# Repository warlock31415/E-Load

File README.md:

# E-Load
An electronic load based on the STM32F103C8T6 chip

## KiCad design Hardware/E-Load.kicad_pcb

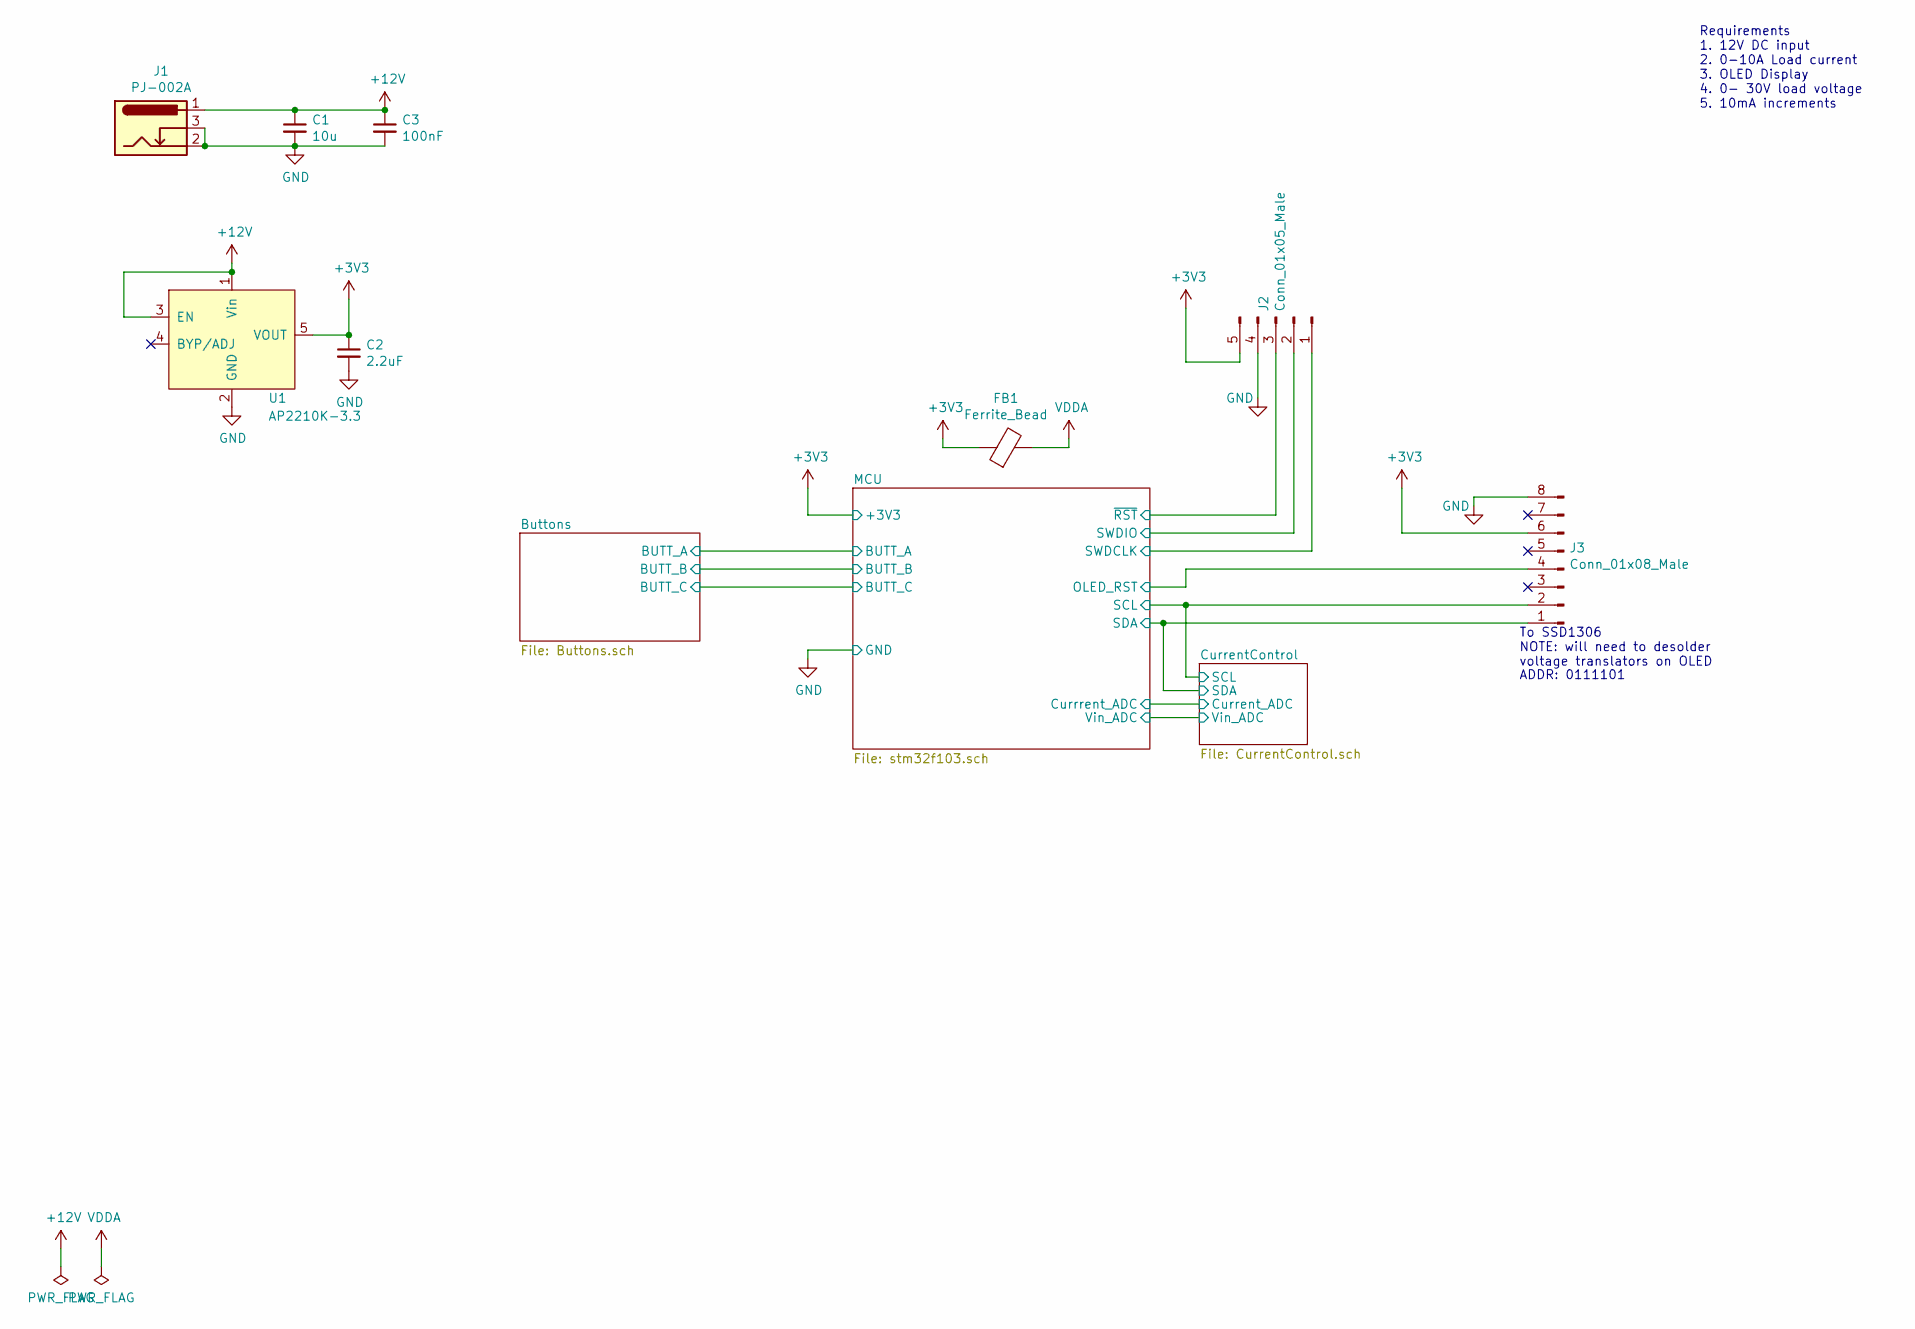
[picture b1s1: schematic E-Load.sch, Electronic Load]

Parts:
C1: 10u; CP_Radial_D5.0mm_P2.50mm; Digikey 732-8937-1-ND
C2: 2.2uF; C_0603_1608Metric_Pad1.05x0.95mm_HandSolder; LCSC C92783
C3: 100nF; C_0603_1608Metric_Pad1.05x0.95mm_HandSolder; LCSC C1591
FB1: Ferrite_Bead; C_1206_3216Metric; LCSC C16902
J1: PJ-002A; BarrelJack_Wuerth_6941xx301002; Digikey CP-002A-ND
J2: Conn_01x05_Male; PinHeader_1x05_P2.54mm_Vertical; LCSC C50981
J3: Conn_01x08_Male; PinHeader_1x08_P2.54mm_Vertical; LCSC C50981
U1: AP2210K-3.3; SOT-23-5_HandSoldering; LCSC C264085

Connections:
+12V: C1.1, C3.1, J1.1, U1.1 (Vin), U1.3 (EN); also elsewhere on the board
/CurrentControl/SCL: J3.2; also elsewhere on the board
/CurrentControl/SDA: J3.1; also elsewhere on the board
/MCU/OLED_RST: J3.4; also elsewhere on the board
/MCU/SWDCLK: J2.1; also elsewhere on the board
/MCU/SWDIO: J2.2; also elsewhere on the board
/MCU/~RST: J2.3; also elsewhere on the board
GND: C1.2, C2.2, C3.2, J1.2, J1.3, J2.4, J3.8, U1.2 (GND); also elsewhere on the board
VDDA: FB1.2; also elsewhere on the board

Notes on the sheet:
Requirements 1. 12V DC input 2. 0-10A Load current 3. OLED Display 4. 0- 30V load voltage 5. 10mA increments
ADDR: 0111101
To SSD1306 NOTE: will need to desolder voltage translators on OLED

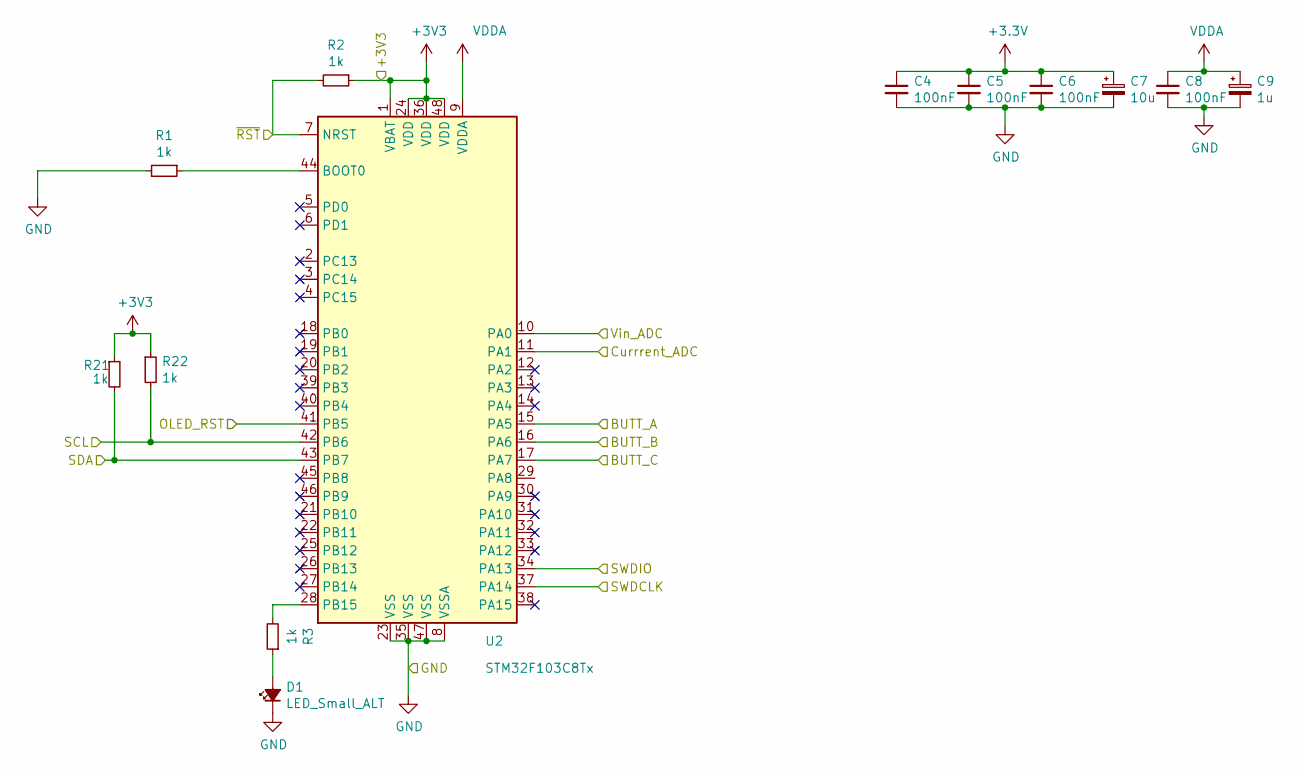
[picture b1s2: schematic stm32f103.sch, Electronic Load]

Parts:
C4, C5, C6, C8: 100nF; C_0603_1608Metric_Pad1.05x0.95mm_HandSolder; LCSC C1591
C7: 10u; CP_Radial_D5.0mm_P2.50mm; Digikey 732-8937-1-ND
C9: 1u; CP_Radial_D5.0mm_P2.50mm; Digikey 732-8851-1-ND
D1: LED_Small_ALT; C_0805_2012Metric_Pad1.15x1.40mm_HandSolder; LCSC C193191
R1, R2, R3, R21, R22: 1k; R_0603_1608Metric_Pad1.05x0.95mm_HandSolder; LCSC C441891
U2: STM32F103C8Tx; LQFP-48_7x7mm_P0.5mm; LCSC C8734

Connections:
/Buttons/BUTT_A: U2.15 (PA5); also elsewhere on the board
/Buttons/BUTT_B: U2.16 (PA6); also elsewhere on the board
/Buttons/BUTT_C: U2.17 (PA7); also elsewhere on the board
/CurrentControl/Current_ADC: U2.11 (PA1); also elsewhere on the board
/CurrentControl/SCL: R22.2, U2.42 (PB6); also elsewhere on the board
/CurrentControl/SDA: R21.2, U2.43 (PB7); also elsewhere on the board
/CurrentControl/Vin_ADC: U2.10 (PA0); also elsewhere on the board
/MCU/OLED_RST: U2.41 (PB5); also elsewhere on the board
/MCU/SWDCLK: U2.37 (PA14); also elsewhere on the board
/MCU/SWDIO: U2.34 (PA13); also elsewhere on the board
/MCU/~RST: R2.2, U2.7 (NRST); also elsewhere on the board
GND: C4.2, C5.2, C6.2, C7.2, C8.2, C9.2, D1.1 (K), R1.2, U2.8 (VSSA), U2.23 (VSS), U2.35 (VSS), U2.47 (VSS); also elsewhere on the board
unnamed: D1.2 (A), R3.1
unnamed: R1.1, U2.44 (BOOT0)
unnamed: R3.2, U2.28 (PB15)
VDDA: C8.1, C9.1, U2.9 (VDDA); also elsewhere on the board

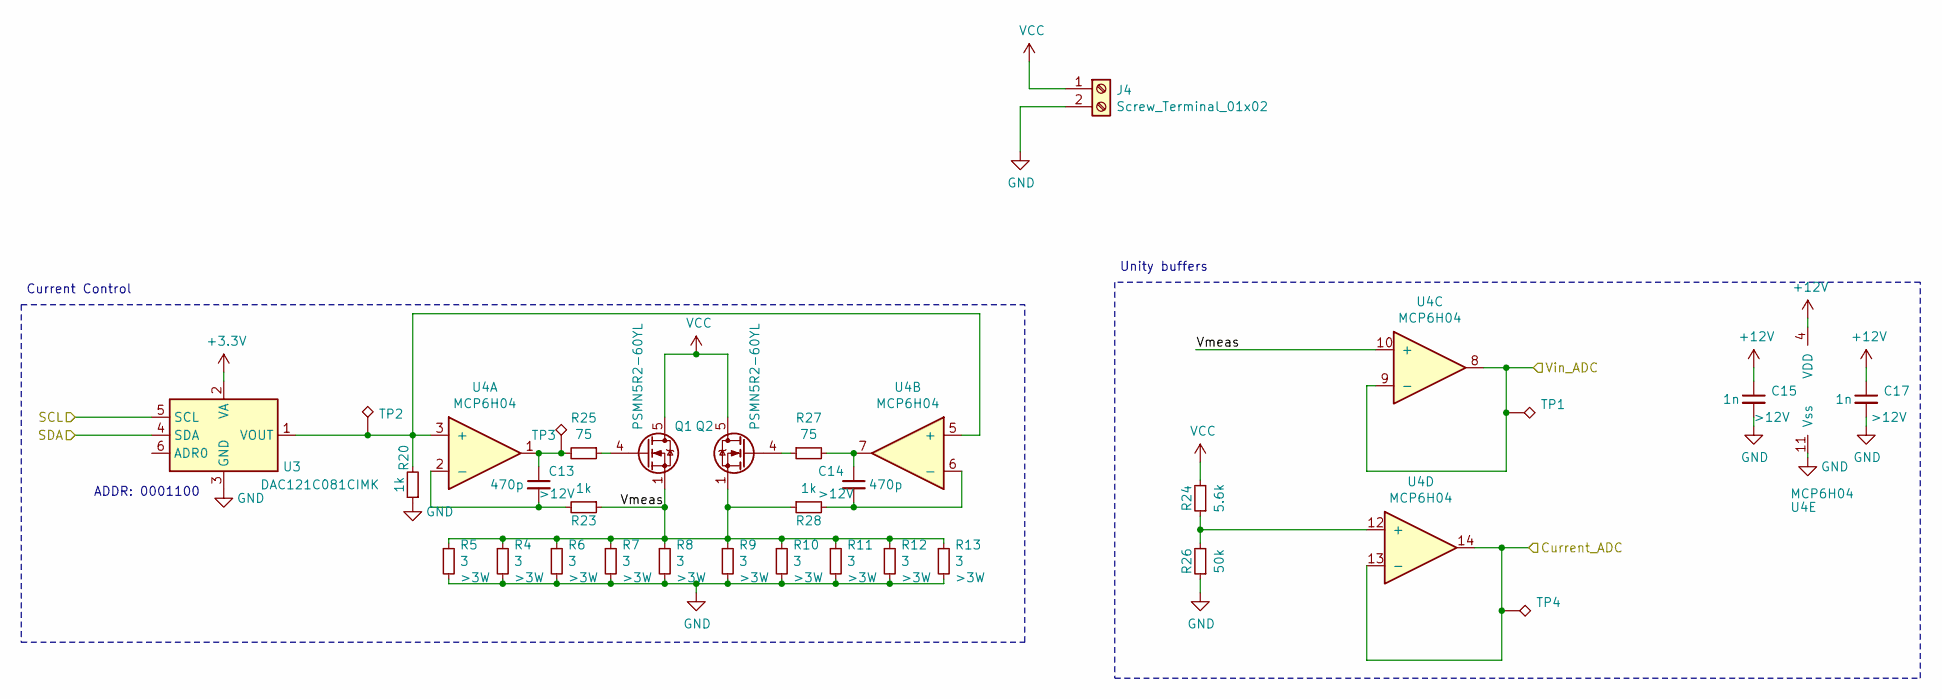
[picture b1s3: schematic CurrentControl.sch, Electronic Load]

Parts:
C13, C14: 470p; C_0603_1608Metric_Pad1.05x0.95mm_HandSolder; Voltage >12V; LCSC C376836
C15, C17: 1n; C_0603_1608Metric_Pad1.05x0.95mm_HandSolder; Voltage >12V; LCSC C100040
J4: Screw_Terminal_01x02; PhoenixContact_MCV_1,5_2-G-3.81_1x02_P3.81mm_Vertical; LCSC C89123
Q1, Q2: PSMN5R2-60YL; LFPAK56; Digikey 1727-2595-1-ND
R4, R5, R6, R7, R8, R9, R10, R11, R12, R13: 3; R_Axial_DIN0614_L14.3mm_D5.7mm_P25.40mm_Horizontal; Digikey PPC5W3.0CT-ND
R20, R23, R28: 1k; R_0603_1608Metric_Pad1.05x0.95mm_HandSolder; LCSC C441891
R24: 5.6k; R_0603_1608Metric_Pad1.05x0.95mm_HandSolder; LCSC C507469
R25, R27: 75; R_0603_1608Metric_Pad1.05x0.95mm_HandSolder; LCSC C441884
R26: 50k; R_0603_1608Metric_Pad1.05x0.95mm_HandSolder; LCSC C881419
TP1, TP2, TP3, TP4: TestPoint_Alt; TestPoint_Keystone_5000-5004_Miniature
U3: DAC121C081CIMK; SOT-23-6; Digikey DAC121C081CIMK/NOPBCT-ND
U4: MCP6H04; TSSOP-14_4.4x5mm_P0.65mm; Digikey MCP6H04T-E/SLCT-ND

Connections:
+12V: C15.1, C17.1, U4.4 (VDD); also elsewhere on the board
/CurrentControl/Current_ADC: TP4.1, U4.13 (-), U4.14; also elsewhere on the board
/CurrentControl/SCL: U3.5 (SCL); also elsewhere on the board
/CurrentControl/SDA: U3.4 (SDA); also elsewhere on the board
/CurrentControl/Vin_ADC: TP1.1, U4.8, U4.9 (-); also elsewhere on the board
/CurrentControl/Vmeas: Q1.1 (S), Q1.2 (S), Q1.3 (S), Q2.1 (S), Q2.2 (S), Q2.3 (S), R4.1, R5.1, R6.1, R7.1, R8.1, R9.1, R10.1, R11.1, R12.1, R13.1, R23.1, R28.1, U4.10 (+)
GND: C15.2, C17.2, J4.2, R4.2, R5.2, R6.2, R7.2, R8.2, R9.2, R10.2, R11.2, R12.2, R13.2, R20.1, R26.1, U3.3 (GND), U4.11 (Vss); also elsewhere on the board
unnamed: C13.1, R25.2, TP3.1, U4.1
unnamed: C13.2, R23.2, U4.2 (-)
unnamed: C14.1, R27.2, U4.7
unnamed: C14.2, R28.2, U4.6 (-)
unnamed: Q1.4 (G), R25.1
unnamed: Q2.4 (G), R27.1
unnamed: R20.2, TP2.1, U3.1 (VOUT), U4.3 (+), U4.5 (+)
unnamed: R24.1, R26.2, U4.12 (+)
VCC: J4.1, Q1.5 (D), Q2.5 (D), R24.2

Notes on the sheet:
Unity buffers
Current Control
ADDR: 0001100

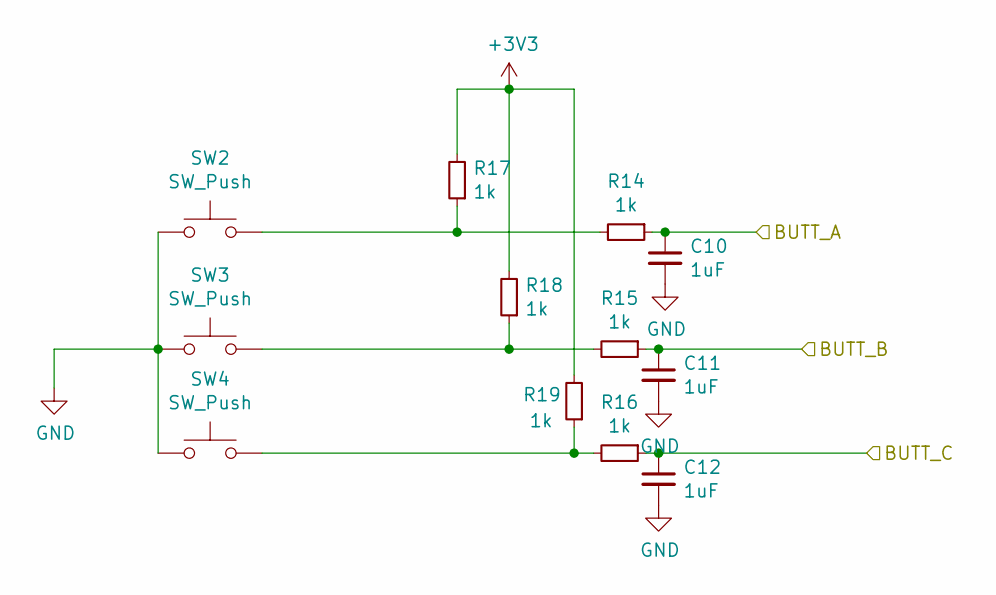
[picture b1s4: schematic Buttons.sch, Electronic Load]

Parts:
C10, C11, C12: 1uF; C_0603_1608Metric_Pad1.05x0.95mm_HandSolder; LCSC C696843
R14, R15, R16, R17, R18, R19: 1k; R_0603_1608Metric_Pad1.05x0.95mm_HandSolder; LCSC C441891
SW2: SW_Push; SW_PUSH_6mm_H4.3mm; Digikey CKN9078-ND
SW3, SW4: SW_Push; SW_PUSH_6mm_H4.3mm; LCSC C221879

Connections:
/Buttons/BUTT_A: C10.1, R14.1; also elsewhere on the board
/Buttons/BUTT_B: C11.1, R15.1; also elsewhere on the board
/Buttons/BUTT_C: C12.1, R16.1; also elsewhere on the board
GND: C10.2, C11.2, C12.2, SW2.1, SW3.1, SW4.1; also elsewhere on the board
unnamed: R14.2, R17.1, SW2.2
unnamed: R15.2, R18.1, SW3.2
unnamed: R16.2, R19.1, SW4.2

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
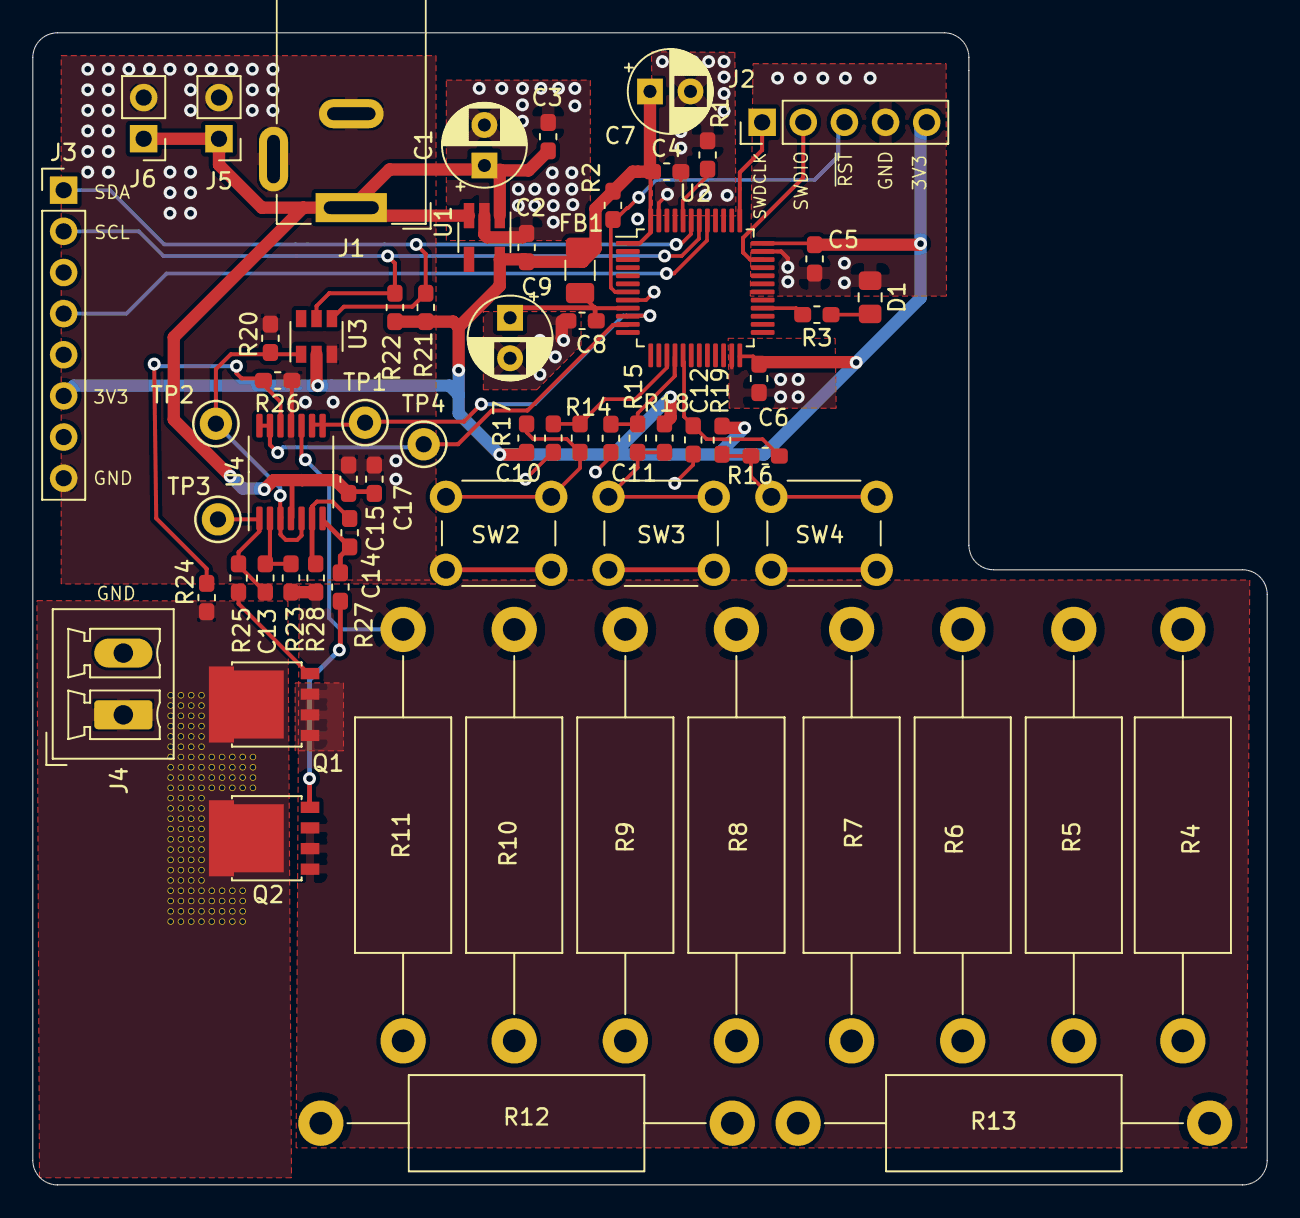
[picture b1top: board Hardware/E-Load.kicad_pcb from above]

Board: 2 copper layers, 76.2 x 71.1 mm, 65 parts (0 on the bottom side), 31 nets.

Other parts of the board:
J5, J6: Conn_01x02_Male; PinHeader_1x02_P2.54mm_Vertical

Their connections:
+12V: J5.1, J6.1; also elsewhere on the board
GND: J5.2, J6.2; also elsewhere on the board

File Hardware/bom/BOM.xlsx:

| Sourced | Placed | References | Value | Footprint | Quantity | Digikey Part Number
1 |  |  | C7 | 10u | CP_Radial_D5.0mm_P2.50mm | 1 | 732-8937-1-ND
2 |  |  | C9 | 1u | CP_Radial_D5.0mm_P2.50mm | 1 | 732-8851-1-ND
3 |  |  | C3, C4, C5, C6, C8, C10 | 100nF | C_0603_1608Metric_Pad1.05x0.95mm_HandSolder | 6 | 399-1099-1-ND
4 |  |  | C15, C16, C17 | 1n | C_0603_1608Metric_Pad1.05x0.95mm_HandSolder | 3 | 1292-1380-1-ND
5 |  |  | C11, C12 | 1uF | C_0603_1608Metric_Pad1.05x0.95mm_HandSolder | 2 | 1276-1184-1-ND
6 |  |  | C1 | 10u | C_0603_1608Metric_Pad1.05x0.95mm_HandSolder | 1 | 732-8937-1-ND
7 |  |  | C2 | 2.2uF | C_0603_1608Metric_Pad1.05x0.95mm_HandSolder | 1 | 587-5835-1-ND
8 |  |  | R1, R2, R3, R14, R15, R16, R17, R18, R19, R20, R21, R22 | 1k | R_0603_1608Metric_Pad1.05x0.95mm_HandSolder | 12 | 118-CR0603AFX-1001ELFCT-ND
9 |  |  | R25 | 50 | R_0603_1608Metric_Pad1.05x0.95mm_HandSolder | 1 | 541-3318-1-ND
10 |  |  | R4, R5, R6, R7, R8, R9, R10, R11, R12, R13 | 3 | R_Axial_DIN0614_L14.3mm_D5.7mm_P25.40mm_Horizontal | 10 | PPC5W3.0CT-ND
11 |  |  | D1 | LED_Small_ALT | C_0805_2012Metric_Pad1.15x1.40mm_HandSolder | 1 | 732-12016-1-ND
12 |  |  | U2 | STM32F103C8Tx | LQFP-48_7x7mm_P0.5mm | 1 | 497-11517-ND
13 |  |  | U1 | AP2210K-3.3 | SOT-23-5_HandSoldering | 1 | AP2210K-3.3TRG1DICT-ND
14 |  |  | U3 | DAC121C081CIMK | SOT-23-6 | 1 | DAC121C081CIMK/NOPBCT-ND
15 |  |  | U4, U5 | TLV172IDCK | SOT-353_SC-70-5 | 2 | 296-48697-1-ND
16 |  |  | SW2, SW3, SW4 | SW_Push | SW_PUSH_6mm_H4.3mm | 3 | CKN9078-ND
17 |  |  | FB1 | Ferrite_Bead | C_1206_3216Metric | 1 | 490-5229-1-ND
18 |  |  | Q1 | BUK7M45-40EX | LFPAK33 | 1 | 1727-2563-1-ND
19 |  |  | TP2, TP3, TP4 | TestPoint_Alt | TestPoint_Keystone_5000-5004_Miniature | 3 | NA
20 |  |  | J1 | PJ-002A | BarrelJack_Wuerth_6941xx301002 | 1 | CP-002A-ND
21 |  |  | J2 | Conn_01x05_Male | PinHeader_1x05_P2.54mm_Vertical | 1 | 609-6372-ND
22 |  |  | J3 | Conn_01x08_Male | PinHeader_1x08_P2.54mm_Vertical | 1 | USE ABOVE
23 |  |  | J4 | Screw_Terminal_01x03 | TE_826576-3_1x03_P3.96mm_Vertical | 1 | 277-6072-ND

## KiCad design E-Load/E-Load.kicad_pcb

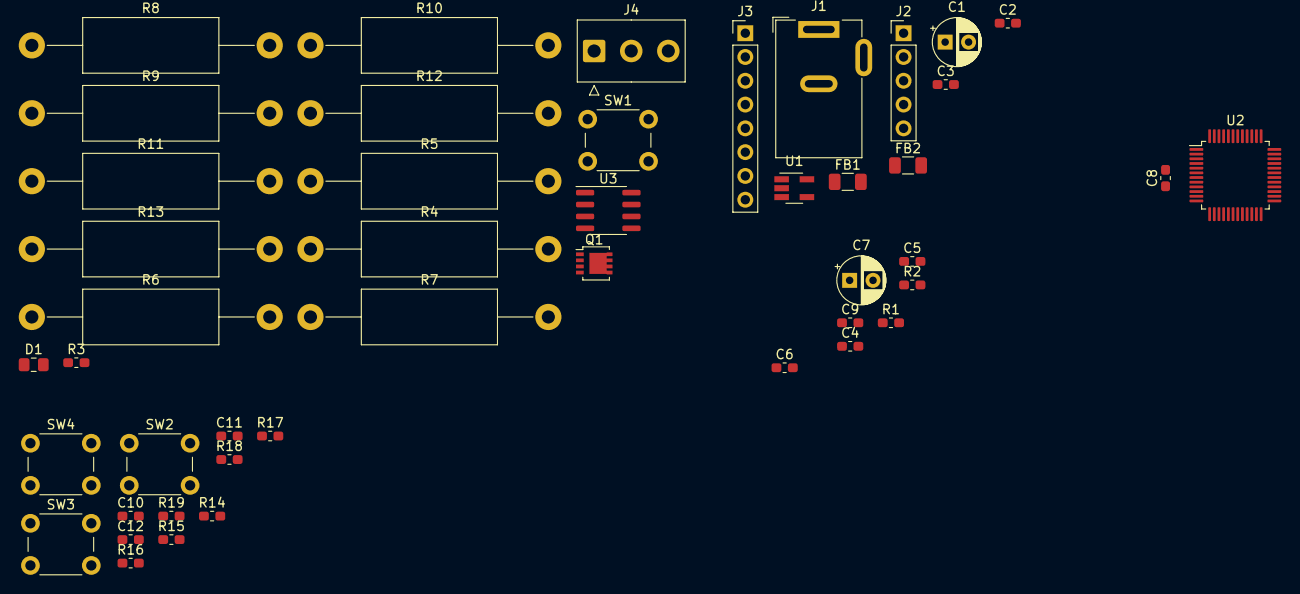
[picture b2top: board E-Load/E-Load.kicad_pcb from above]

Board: 2 copper layers, 46 parts (0 on the bottom side), 23 nets, no tracks yet.

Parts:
C1, C7: 10u; CP_Radial_D5.0mm_P2.50mm
C2: 2.2uF; C_0603_1608Metric_Pad1.05x0.95mm_HandSolder
C3, C10: 0.1uF; C_0603_1608Metric_Pad1.05x0.95mm_HandSolder
C4, C5, C6, C8: 100nF; C_0603_1608Metric_Pad1.05x0.95mm_HandSolder
C9: 1u; C_0603_1608Metric_Pad1.05x0.95mm_HandSolder
C11, C12: 1uF; C_0603_1608Metric_Pad1.05x0.95mm_HandSolder
D1: LED_Small_ALT; C_0805_2012Metric_Pad1.15x1.40mm_HandSolder
FB1, FB2: Ferrite_Bead; C_1206_3216Metric
J1: Barrel_Jack; BarrelJack_Wuerth_6941xx301002
J2: Conn_01x05_Male; PinHeader_1x05_P2.54mm_Vertical
J3: Conn_01x08_Male; PinHeader_1x08_P2.54mm_Vertical
J4: Screw_Terminal_01x03; TE_826576-3_1x03_P3.96mm_Vertical
Q1: BUK7M45-40EX; LFPAK33
R1, R2: 1k; R_0603_1608Metric_Pad1.05x0.95mm_HandSolder
R3, R14, R15, R16, R17, R18, R19: 1K; R_0603_1608Metric_Pad1.05x0.95mm_HandSolder
R4, R5, R6, R7, R8, R9, R10, R11, R12, R13: 3; R_Axial_DIN0614_L14.3mm_D5.7mm_P25.40mm_Horizontal
SW1: SW_SPST; SW_PUSH_6mm_H4.3mm
SW2, SW3, SW4: SW_Push; SW_PUSH_6mm_H4.3mm
U1: AP2210K-3.3; SOT-23-5_HandSoldering
U2: STM32F102C8Tx; LQFP-48_7x7mm_P0.5mm
U3: MCP14A0302; SOIC-8_3.9x4.9mm_P1.27mm

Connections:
+3V3: C2.1, C4.1, C5.1, C6.1, C7.1, FB1.1, J2.5, J3.6, R2.1, R17.2, R18.2, R19.2, U1.5, U2.24, U2.36, U2.48
+12V: C1.1, C3.1, J1.1, SW1.2, U1.1, U1.3, U3.1, U3.8
/Buttons/BUTT_A: C10.1, R14.1, R17.1, U2.15
/Buttons/BUTT_B: C11.1, R15.1, R18.1, U2.16
/Buttons/BUTT_C: C12.1, R16.1, R19.1, U2.17
/CurrentControl/ADC: Q1.1, Q1.2, Q1.3, R4.1, R5.1, R6.1, R7.1, R8.1, R9.1, R10.1, R11.1, R12.1, R13.1, U2.10
/MCU/OLED_RST: J3.4, U2.14
/MCU/SCL: J3.2, U2.42
/MCU/SDA: J3.1, U2.43
/MCU/SWDCLK: J2.1, U2.37
/MCU/SWDIO: J2.2, U2.34
/MCU/~RST: J2.3, R2.2, U2.7
GND: C1.2, C2.2, C3.2, C4.2, C5.2, C6.2, C7.2, C8.2, C9.2, C10.2, C11.2, C12.2, D1.1, FB2.1, J1.2, J2.4, J3.8, R1.2, SW2.1, SW3.1, SW4.1, U1.2, U2.8, U2.23, U2.35, U2.47, U3.4, U3.5
GNDA: FB2.2, J4.3, R4.2, R5.2, R6.2, R7.2, R8.2, R9.2, R10.2, R11.2, R12.2, R13.2
unnamed: D1.2, R3.2
unnamed: Q1.4, U3.6, U3.7
unnamed: R1.1, U2.44
unnamed: R3.1, SW1.1, U3.3
unnamed: R14.2, SW2.2
unnamed: R15.2, SW3.2
unnamed: R16.2, SW4.2
VCC: J4.1, Q1.5
VDDA: C8.1, C9.1, FB1.2, U2.9

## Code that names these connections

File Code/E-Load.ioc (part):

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Mcu.Name=STM32F103C(8-B)Tx
Mcu.Package=LQFP48
Mcu.UserName=STM32F103C8Tx
PA0-WKUP.Signal=ADCx_IN0
PA1.Signal=ADCx_IN1
PA13.GPIOParameters=GPIO_Label
PA13.GPIO_Label=SWDIO
PA13.Mode=Serial_Wire
PA13.Signal=SYS_JTMS-SWDIO
PA14.GPIOParameters=GPIO_Label
PA14.GPIO_Label=SWCLK
PA14.Mode=Serial_Wire
PA14.Signal=SYS_JTCK-SWCLK
PA5.GPIOParameters=GPIO_Label
PA5.GPIO_Label=A
PA5.Signal=GPIO_Input
PA6.GPIOParameters=GPIO_Label
PA6.GPIO_Label=B
PA6.Signal=GPIO_Input
PA7.GPIOParameters=GPIO_Label
PA7.GPIO_Label=C
PA7.Signal=GPIO_Input
PB15.GPIOParameters=GPIO_Label
PB15.GPIO_Label=LED
PB15.Signal=GPIO_Output
PB6.Mode=I2C
PB6.Signal=I2C1_SCL
PB7.Mode=I2C
PB7.Signal=I2C1_SDA
board=custom

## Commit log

2020-10-07 Layed out PCB, Added filter
2020-10-07 Corrected ideal diode
2020-10-08 Replaced gate driver with opamp. Replaced feedback circuit with unity gain buffer
2020-10-08 Changed the PWM control circuit
2020-10-08 Added Test points
2020-10-08 Added ADC instead of opamp. Added stiching
2020-10-08 Minor changes
2020-10-09 Added pull up resistors on I2C line, added BOM
2020-10-09 Extended VCC plane
2020-10-13 updated C1 footprint, updated MCU schematic. Fixed possible issue with buttons
2020-10-29 Initial code commit
    ADC,DAC and button have been tested and working!!
2020-11-03 Added new FET and opamp. Repositioned parts on PCB
2020-11-03 forgot to save
2020-11-05 Added a Quad opamp. fixed cut out, fixed silkscreen issues. Made pin names bigger
2020-11-12 Added LCSC part#, Thermal vias, etc
2020-11-14 Added second mosfet and added FPaste layer on thermal vias
2020-11-26 Added PDF and other cleanup
2020-12-28 Added 2nd ADC channel and DMA
